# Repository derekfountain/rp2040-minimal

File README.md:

# RP2040 Minimal Circuit (Failure)

This is the RP2040 minimal circuit, as linked to from the RP2040
hardware guide. I thought I'd have a go at making it, just to see if
I could.

Spoiler: I couldn't.

## Adaptions

I couldn't find the NCP1117 voltage regulator, so I switched it for
the AZ1117. That's essentially the same device, only it needs a
slightly different value for one of the capacitors.

I also changed their 16MB flash for a 2MB one, which was much
cheaper and adequate for my purposes.

I labelled the revised board v1.1DF and had it made up by JLCPCB.

## Soldering 0402

The 0402 sized components are very fiddly, but not really any
different to the bigger ones. I couldn't use my preferred 3mm iron
tip, I used a 1mm conical one with the iron temperature turned up
to about 335C. I still don't find it easy to get heat into the joint
but it does work. Some components are so close to each other it's
hard to get the tweezer tips in the gaps.

I pulled a pad off the board at C12. They're a lot more fragile than
bigger pads. C12 is only one of many decoupling capactitors, so I
figured I could get away with this one missing.

After soldering those, the joints are greatly improved with a 1 minute
blast of 230C air with a small nozzle, just to melt and reseal the
surface of the solder. That removes the icicles, and any joints that
are dangerously close to each other change into smooth round blobs
which makes inspection much easier.

## Soldering RP2040

The RP2040 was beyond me. My best approach was to use liquid flux on
the pads, then wipe a tinned soldering iron along each pad to wet it.
Then use the hot air again to ensure each pad's tinning was neat.
Getting just the right amount of solder on the ground pad was very
hard. Too little, no joint; too much and the IC sits up proud when
trying to solder it and the air gets underneath. I put some solder on
then wicked off almost all of it with solder braid.  Again, the hot
air evens its up nicely.

For hot air soldering I tried to use a profile like the RP2040 oven
profile. I put the station on 260C, then did:

* 90 seconds at 200C, so I kept the gun some distance away
* 30 seconds at 220C, moving the gun to within 2cm
* 30 seconds at 260C, moving the gun to within 1cm
* 45 seconds slowly bringing the gun away

It's all rather hand-wavy. I've no way of knowing what temperatures
the IC is getting to.

I found wiping a small amount of flux along each side before starting
made the solder apparently melt a little easier, but it's hard to tell.

Keeping the air coming from directly above, the RP2040 solders on
correctly using this approach, and as far as I can see under
magnification it should work, but it doesn't. I must have added and
removed the RP2040 half a dozen times, but I never got one working.
I can probe 3V3 at the IC's power input, but there's nothing on the
crystal driver output, nothing on the SWD, nothing on the 1V1 output,
and the USB doesn't work.

## Failure

Maybe there's a better technique, or maybe I'm cooking the IC. I've
no way to tell. I hate giving up, but this was becoming pointless.
If my experience helps anyone else, well, there's that I suppose.

## Update

My friend, AM, has a bit of experience with soldering QFN-56 packages
in an oven. He tried to solder one of these, plus another one he did
with hot air. Both those failed as well. So I did 2, AM did 2, and
none of them worked.

[Derek Fountain](https://www.derekfountain.org/), February 2024

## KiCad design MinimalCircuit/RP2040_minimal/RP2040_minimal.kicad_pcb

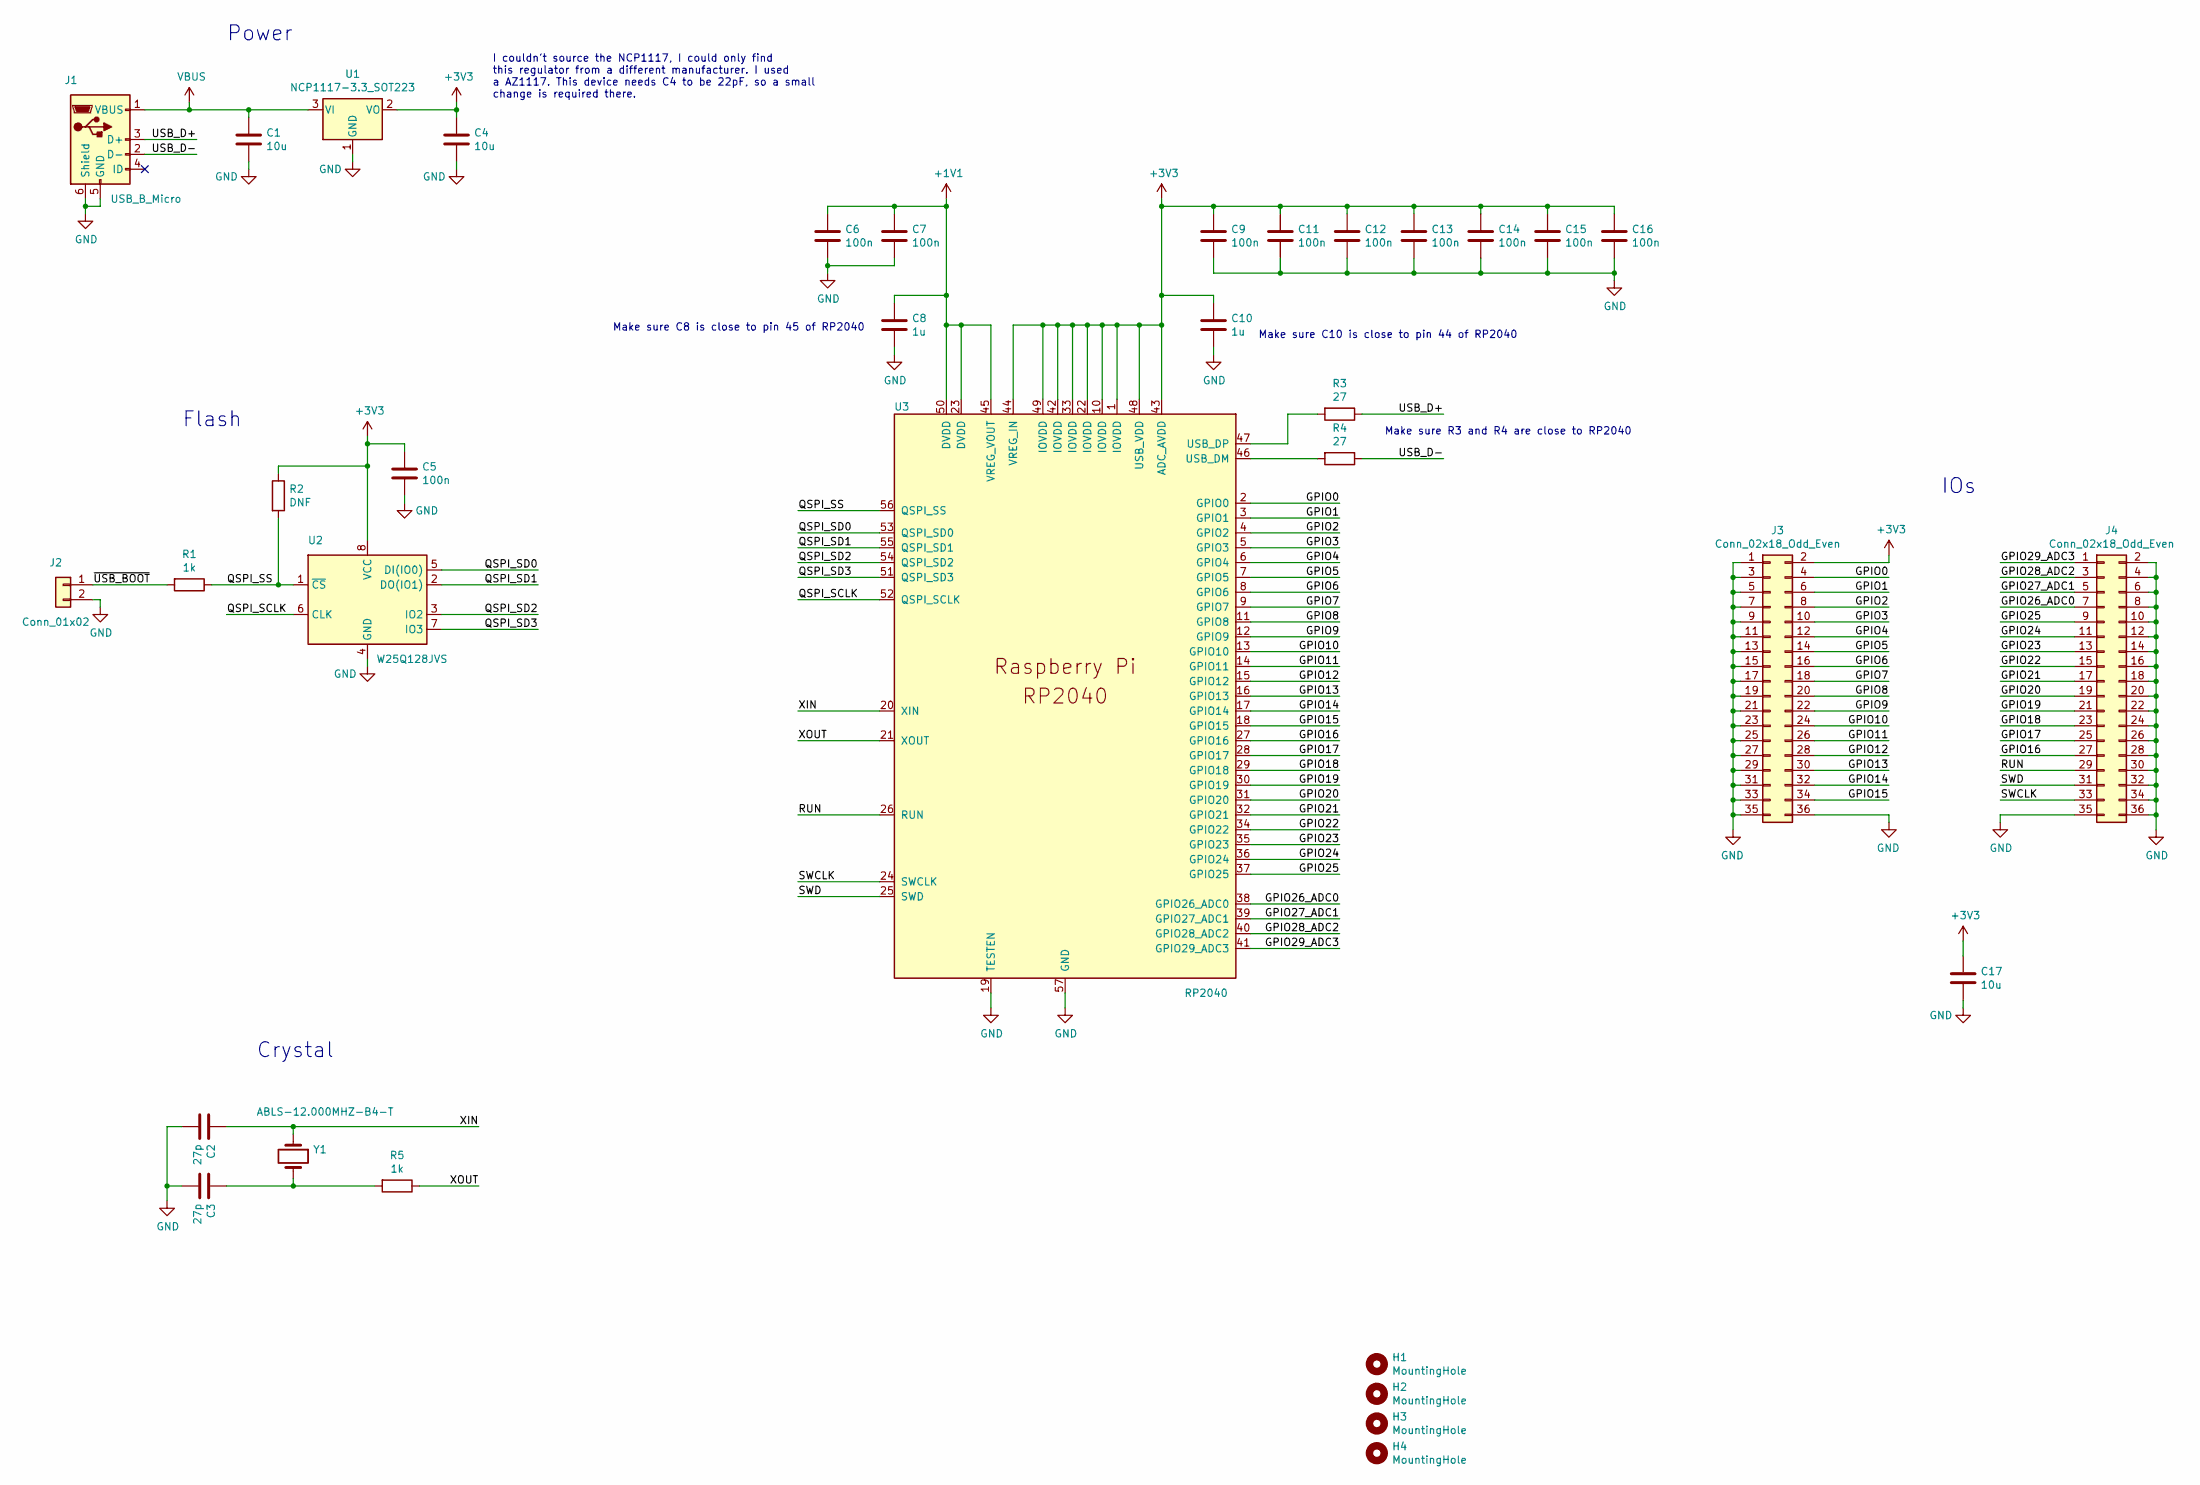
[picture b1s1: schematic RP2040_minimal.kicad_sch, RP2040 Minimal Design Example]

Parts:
C1, C4, C17: 10u; C_0805_2012Metric
C2, C3: 27p; C_0402_1005Metric
C5, C6, C7, C9, C11, C12, C13, C14, C15, C16: 100n; C_0402_1005Metric
C8, C10: 1u; C_0402_1005Metric
H1, H2, H3, H4: MountingHole; MountingHole_2.7mm_M2.5
J1: USB_B_Micro; USB_Micro-B_Amphenol_10103594-0001LF_Horizontal_modified
J2: Conn_01x02; PinHeader_1x02_P2.54mm_Vertical
J3, J4: Conn_02x18_Odd_Even; PinHeader_2x18_P2.54mm_Vertical
R1, R5: 1k; C_0402_1005Metric
R2: DNF; C_0402_1005Metric
R3, R4: 27; C_0402_1005Metric
U1: NCP1117-3.3_SOT223; SOT-223-3_TabPin2
U2: W25Q128JVS; SOIC-8_5.23x5.23mm_P1.27mm
U3: RP2040; RP2040-QFN-56
Y1: ABLS-12.000MHZ-B4-T; Crystal_SMD_HC49-US

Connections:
+1V1: C6.1, C7.1, C8.1, U3.23 (DVDD), U3.45 (VREG_VOUT), U3.50 (DVDD)
+3V3: C4.1, C5.1, C9.1, C10.1, C11.1, C12.1, C13.1, C14.1, C15.1, C16.1, C17.1, J3.2, R2.1, U1.2 (VO), U2.8 (VCC), U3.1 (IOVDD), U3.10 (IOVDD), U3.22 (IOVDD), U3.33 (IOVDD), U3.42 (IOVDD), U3.43 (ADC_AVDD), U3.44 (VREG_IN), U3.48 (USB_VDD), U3.49 (IOVDD)
/GPIO0: J3.4, U3.2 (GPIO0)
/GPIO1: J3.6, U3.3 (GPIO1)
/GPIO2: J3.8, U3.4 (GPIO2)
/GPIO3: J3.10, U3.5 (GPIO3)
/GPIO4: J3.12, U3.6 (GPIO4)
/GPIO5: J3.14, U3.7 (GPIO5)
/GPIO6: J3.16, U3.8 (GPIO6)
/GPIO7: J3.18, U3.9 (GPIO7)
/GPIO8: J3.20, U3.11 (GPIO8)
/GPIO9: J3.22, U3.12 (GPIO9)
/GPIO10: J3.24, U3.13 (GPIO10)
/GPIO11: J3.26, U3.14 (GPIO11)
/GPIO12: J3.28, U3.15 (GPIO12)
/GPIO13: J3.30, U3.16 (GPIO13)
/GPIO14: J3.32, U3.17 (GPIO14)
/GPIO15: J3.34, U3.18 (GPIO15)
/GPIO16: J4.27, U3.27 (GPIO16)
/GPIO17: J4.25, U3.28 (GPIO17)
/GPIO18: J4.23, U3.29 (GPIO18)
/GPIO19: J4.21, U3.30 (GPIO19)
/GPIO20: J4.19, U3.31 (GPIO20)
/GPIO21: J4.17, U3.32 (GPIO21)
/GPIO22: J4.15, U3.34 (GPIO22)
/GPIO23: J4.13, U3.35 (GPIO23)
/GPIO24: J4.11, U3.36 (GPIO24)
/GPIO25: J4.9, U3.37 (GPIO25)
/GPIO26_ADC0: J4.7, U3.38 (GPIO26_ADC0)
/GPIO27_ADC1: J4.5, U3.39 (GPIO27_ADC1)
/GPIO28_ADC2: J4.3, U3.40 (GPIO28_ADC2)
/GPIO29_ADC3: J4.1, U3.41 (GPIO29_ADC3)
/QSPI_SCLK: U2.6 (CLK), U3.52 (QSPI_SCLK)
/QSPI_SD0: U2.5 (DI(IO0)), U3.53 (QSPI_SD0)
/QSPI_SD1: U2.2 (DO(IO1)), U3.55 (QSPI_SD1)
/QSPI_SD2: U2.3 (IO2), U3.54 (QSPI_SD2)
/QSPI_SD3: U2.7 (IO3), U3.51 (QSPI_SD3)
/QSPI_SS: R1.1, R2.2, U2.1 (~CS), U3.56 (QSPI_SS)
/RUN: J4.29, U3.26 (RUN)
/SWCLK: J4.33, U3.24 (SWCLK)
/SWD: J4.31, U3.25 (SWD)
/USB_D+: J1.3 (D+), R3.1
/USB_D-: J1.2 (D-), R4.1
/XIN: C2.1, U3.20 (XIN), Y1.1
/XOUT: R5.1, U3.21 (XOUT)
/~USB_BOOT: J2.1, R1.2
GND: C1.2, C2.2, C3.2, C4.2, C5.2, C6.2, C7.2, C8.2, C9.2, C10.2, C11.2, C12.2, C13.2, C14.2, C15.2, C16.2, C17.2, J1.5 (GND), J1.6 (Shield), J2.2, J3.1, J3.3, J3.5, J3.7, J3.9, J3.11, J3.13, J3.15, J3.17, J3.19, J3.21, J3.23, J3.25, J3.27, J3.29, J3.31, J3.33, J3.35, J3.36, J4.2, J4.4, J4.6, J4.8, J4.10, J4.12, J4.14, J4.16, J4.18, J4.20, J4.22, J4.24, J4.26, J4.28, J4.30, J4.32, J4.34, J4.35, J4.36, U1.1 (GND), U2.4 (GND), U3.19 (TESTEN), U3.57 (GND)
unnamed: C3.1, R5.2, Y1.2
unnamed: R3.2, U3.47 (USB_DP)
unnamed: R4.2, U3.46 (USB_DM)
VBUS: C1.1, J1.1 (VBUS), U1.3 (VI)

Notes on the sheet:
Make sure C8 is close to pin 45 of RP2040
IOs
Flash
Power
Crystal
Make sure C10 is close to pin 44 of RP2040
I couldn't source the NCP1117, I could only find this regulator from a different manufacturer. I used a AZ1117. This device needs C4 to be 22pF, so a small change is required there.
Make sure R3 and R4 are close to RP2040

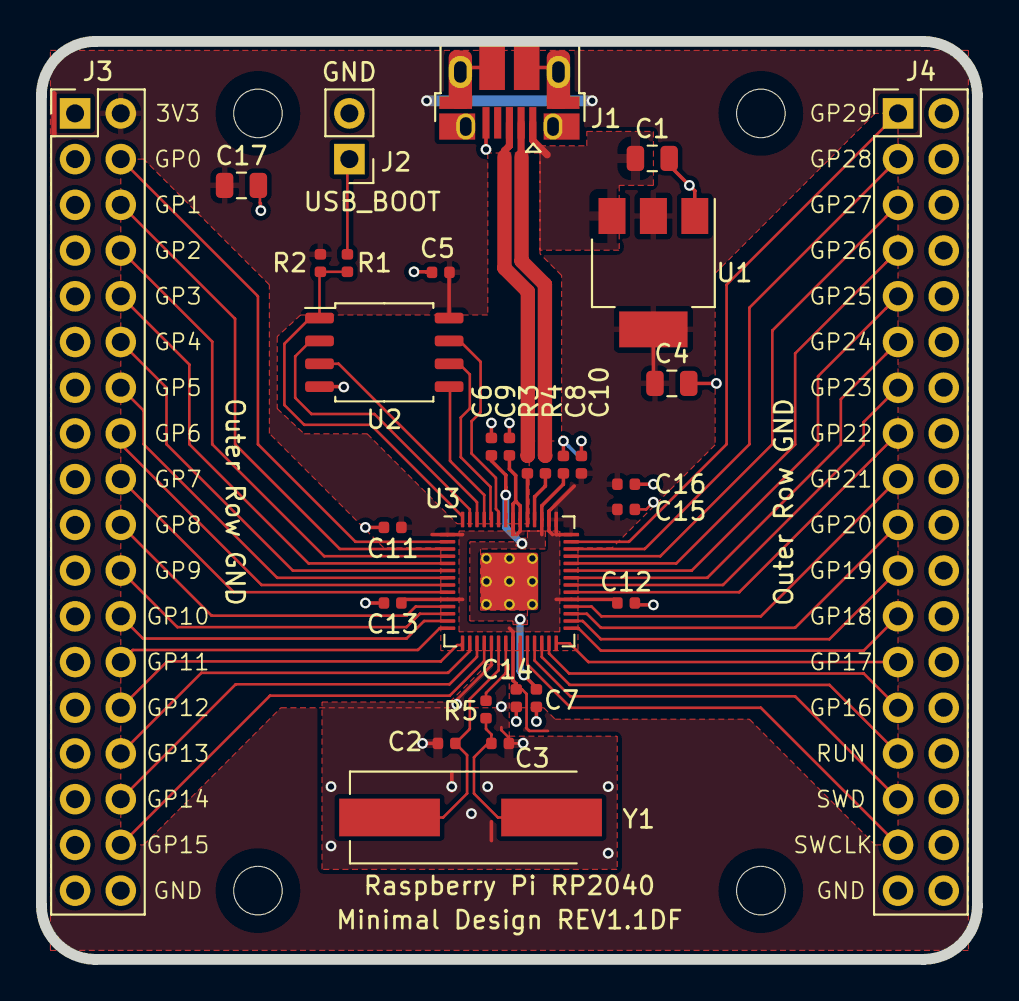
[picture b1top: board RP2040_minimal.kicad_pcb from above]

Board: 2 copper layers, 52.0 x 51.0 mm, 34 parts (0 on the bottom side), 51 nets.
